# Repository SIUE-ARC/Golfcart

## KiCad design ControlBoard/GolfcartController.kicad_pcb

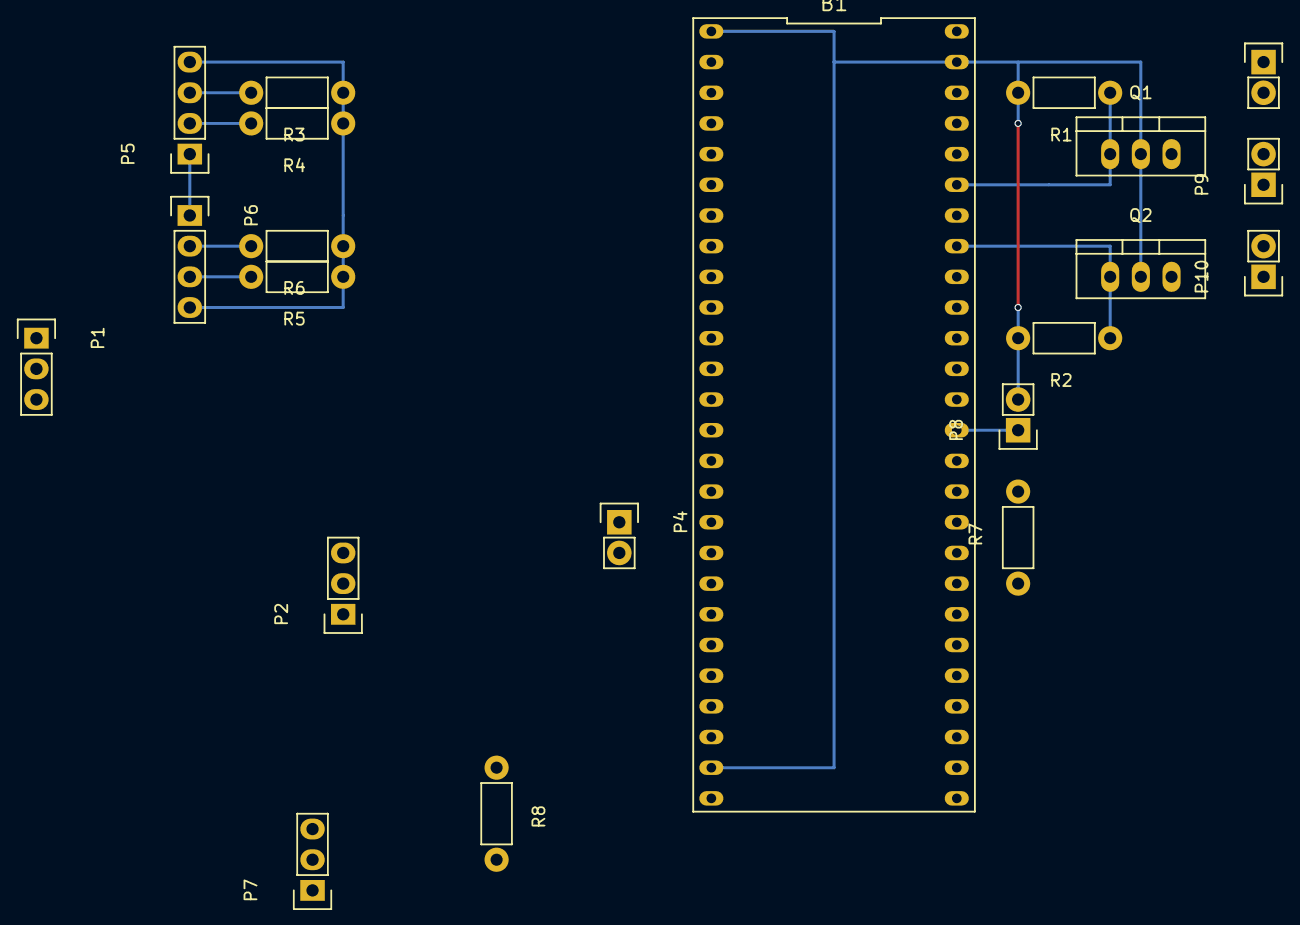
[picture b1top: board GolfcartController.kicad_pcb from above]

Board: 2 copper layers, 21 parts (0 on the bottom side), 16 nets.

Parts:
B1: PSoC5_Dev1; PSoC5_Dev
P1: Steer_Pot; Socket_Strip_Straight_1x03
P2: Brake_Pot; Socket_Strip_Straight_1x03
P3: PSU; Socket_Strip_Straight_1x02
P4: Drive_Controller; Socket_Strip_Straight_1x02
P5: Steer_Enc; Socket_Strip_Straight_1x04
P6: Drive_Enc; Socket_Strip_Straight_1x04
P7: Estop; Socket_Strip_Straight_1x03
P8: SabertoothSerial; Socket_Strip_Straight_1x02
P9, P10: Coast_Relay; Socket_Strip_Straight_1x02
Q1, Q2: Q_NMOS_GDS; TO-220_Neutral123_Vertical
R1, R2, R3, R4, R5, R6, R7, R8: 10k; Resistor_Horizontal_RM7mm

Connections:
+5V: B1.26, B1.52, P1.3, P2.3, P5.4, P6.4, P7.3, R3.1, R4.1, R5.1, R6.1, R7.1
+12V: P3.2, P9.2, P10.2
BrakePot: B1.20, P2.2
Coast: B1.47, Q1.1, R1.1
DriveEncA: B1.22, P6.3, R5.2
DriveEncB: B1.10, P6.2, R6.2
DriveSpeed: B1.17, P4.1
Estop: B1.23, P7.2, R8.1
GND: B1.1, B1.25, B1.51, P1.1, P2.1, P3.1, P4.2, P5.1, P6.1, P7.1, P8.2, Q1.2, Q2.2, R1.2, R2.2, R8.2
unnamed: P9.1, Q1.3
unnamed: P10.1, Q2.3
Reverse: B1.45, Q2.1, R2.1
SteerEncA: B1.6, P5.3, R3.2
SteerEncB: B1.13, P5.2, R4.2
SteerPot: B1.7, P1.2
Tx: B1.39, P8.1, R7.2

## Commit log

2015-10-30 PSoC Documentation
2015-11-20 New Files
2015-11-20 stuff
2015-11-20 Added globals
2015-11-20 Added Halt and floored values that are transmitted.
2015-11-20 New min_move_speed
2015-11-20 Adding PSOC Programs.
2015-11-20 Added convert_angle function for turning to a count correctly.
2015-11-22 New GUI version of Controller Driver
2015-11-22 Get a response after sending commands, Call function when the controller is disconnected
2015-11-22 Require Gtk 3.0
2015-11-22 Empty Keyboard input
2015-11-22 Toggle Buttons for both Drive and Steer Ports
2015-11-22 I HATE HUGE BUTTONS
2015-12-10 White Board Backups
2016-09-02 Cleaned up master and made a legacy branch for all of the old work.
2016-09-02 Updated PSoC node documentation.
2016-09-11 Added tolerance to encoder turn
2016-09-14 Added joystick control
2016-09-14 Fixed elif
2016-09-14 Fixed mising import
2016-09-14 Fixed type error
2016-09-16 Local changes to joystick drive
2016-09-16 Added coast to joystick drive
2016-09-18 Added math to caclulate wheel angle from steering angle
2016-09-18 Deleted catkin output and added gitignore
2016-09-18 Minor refactor and switched to double precision
2016-09-20 Fixed coasting bug in joystick control
2016-09-21 Push from windows partition on Ubuntu
2016-09-21 Made sendStop command take an address input. Attempted fix at the brake fucntion causing blocking behaviour.
2016-09-22 Refactored steer PSoC motor controller handling
2016-09-22 Removed build files from steering psoc project
2016-09-25 More refactoring
2016-09-25 Retabbed main.c in steer psoc
2016-09-25 Refactored serial command handling in steer psoc
2016-09-25 Increased encoder precision on steer psoc
2016-09-25 Added catch all to steer psoc encoder interrupt
2016-09-25 Fixed compile error in steer psoc
2016-09-25 Added flag to steer psoc to wait for motor initilization
2016-09-27 Added stop before direction change in steering PSoC
2016-09-27 Condensed psoc code into single workspace
2016-09-27 Modified steer encoder interrupts to occur on every edge
2016-10-07 Started PSoC 5 workspace
2016-10-07 Hardware setup started
2016-10-07 Finished preliminary PSoC5 schematics.
2016-10-08 Updated DMA stuff
2016-10-11 Messed with USB unsusccessfully
2016-10-12 USB enumerates and powers!
2016-10-12 USB under test.
2016-10-12 Added python test script for USB
2016-10-12 Updated DMA setup
2016-10-14 USB works, ADC->DMA does not and is under test.
2016-10-14 USB working. ADC working. ADC->DMA under test.
2016-10-15 Cleaning up unnecessary filed
2016-10-15 Removed generated source from being tracked.
2016-10-15 Removed asm debugging files.
2016-10-15 ADC->DMA gets some values now. But I have no idea what it's getting values from, and the values do not change
2016-10-26 Updated pinout
2016-10-28 Refactored and started porting PSoC1 code
2016-11-04 Initial control board design
2016-11-15 oops forget to push
2016-11-15 Added more commmands and refactored
2016-11-24 Built up most of the code. #defines still need to be implemented
2016-11-24 Oops typo
2016-12-02 USB commands under test
